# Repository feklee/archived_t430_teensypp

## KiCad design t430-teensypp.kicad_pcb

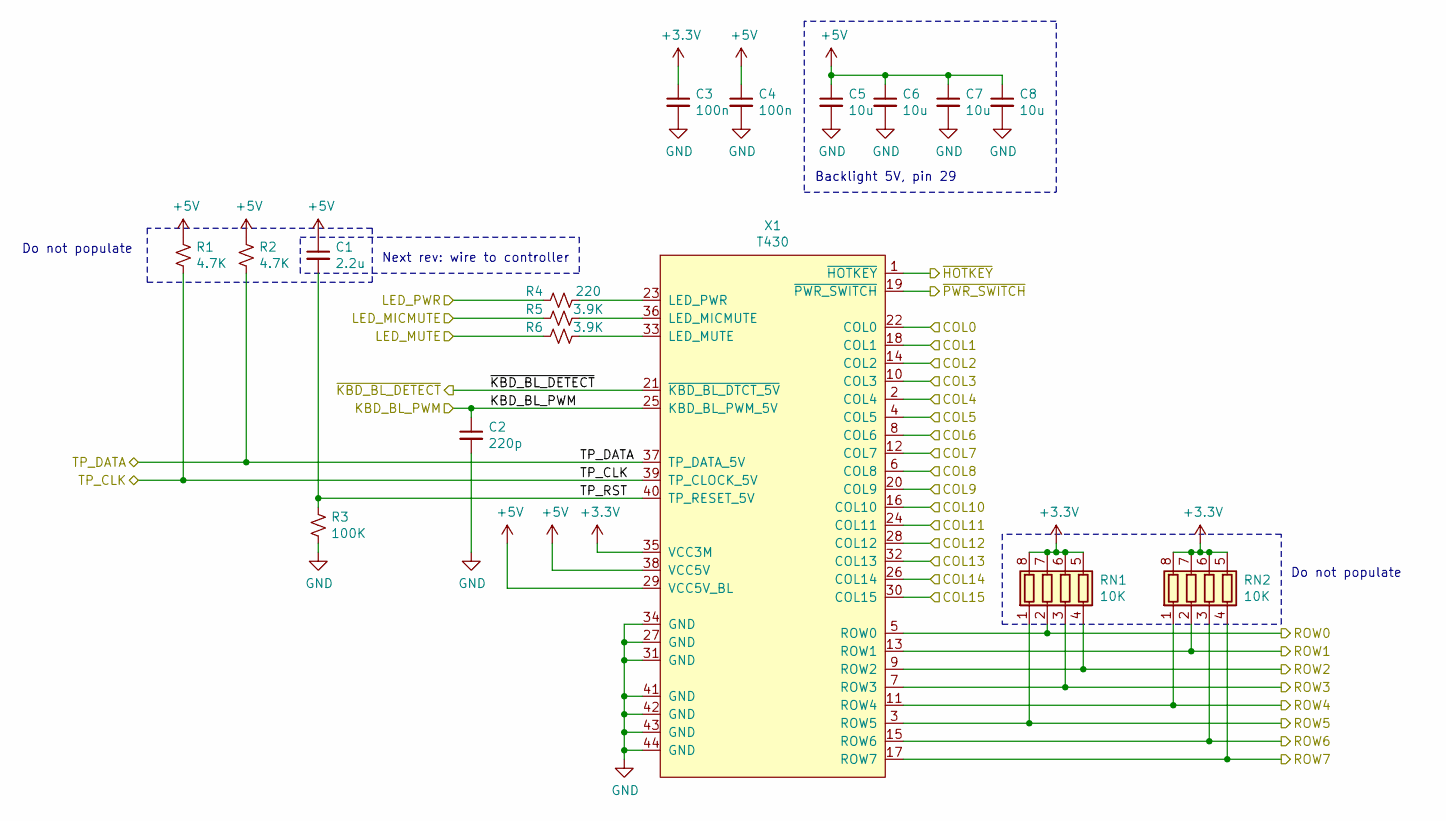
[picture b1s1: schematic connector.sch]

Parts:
C1: 2.2u; C_0805_2012Metric_Pad1.15x1.40mm_HandSolder
C2: 220p; C_0603_1608Metric
C3, C4: 100n; C_0603_1608Metric
C5, C6, C7, C8: 10u; C_0805_2012Metric_Pad1.15x1.40mm_HandSolder
R1, R2: 4.7K; R_0603_1608Metric_Pad1.05x0.95mm_HandSolder
R3: 100K; R_0603_1608Metric_Pad1.05x0.95mm_HandSolder
R4: 220; R_0603_1608Metric_Pad1.05x0.95mm_HandSolder
R5, R6: 3.9K; R_0603_1608Metric_Pad1.05x0.95mm_HandSolder
RN1, RN2: 10K; R_Array_Concave_4x0603
X1: T430

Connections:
+3V3: C3.1, RN1.5 (R4.2), RN1.6 (R3.2), RN1.7 (R2.2), RN1.8 (R1.2), RN2.5 (R4.2), RN2.6 (R3.2), RN2.7 (R2.2), RN2.8 (R1.2), X1.35 (VCC3M); also elsewhere on the board
+5V: C1.1, C4.1, C5.1, C6.1, C7.1, C8.1, R1.1, R2.1, X1.29 (VCC5V_BL), X1.38 (VCC5V); also elsewhere on the board
/Teensy2.0++/COL0: X1.22 (COL0); also elsewhere on the board
/Teensy2.0++/COL1: X1.18 (COL1); also elsewhere on the board
/Teensy2.0++/COL2: X1.14 (COL2); also elsewhere on the board
/Teensy2.0++/COL3: X1.10 (COL3); also elsewhere on the board
/Teensy2.0++/COL4: X1.2 (COL4); also elsewhere on the board
/Teensy2.0++/COL5: X1.4 (COL5); also elsewhere on the board
/Teensy2.0++/COL6: X1.8 (COL6); also elsewhere on the board
/Teensy2.0++/COL7: X1.12 (COL7); also elsewhere on the board
/Teensy2.0++/COL8: X1.6 (COL8); also elsewhere on the board
/Teensy2.0++/COL9: X1.20 (COL9); also elsewhere on the board
/Teensy2.0++/COL10: X1.16 (COL10); also elsewhere on the board
/Teensy2.0++/COL11: X1.24 (COL11); also elsewhere on the board
/Teensy2.0++/COL12: X1.28 (COL12); also elsewhere on the board
/Teensy2.0++/COL13: X1.32 (COL13); also elsewhere on the board
/Teensy2.0++/COL14: X1.26 (COL14); also elsewhere on the board
/Teensy2.0++/COL15: X1.30 (COL15); also elsewhere on the board
/Teensy2.0++/KBD_BL_PWM: C2.1, X1.25 (KBD_BL_PWM_5V); also elsewhere on the board
/Teensy2.0++/LED_MICMUTE: R5.2; also elsewhere on the board
/Teensy2.0++/LED_MUTE: R6.2; also elsewhere on the board
/Teensy2.0++/LED_PWR: R4.2; also elsewhere on the board
/Teensy2.0++/ROW0: RN1.2 (R2.1), X1.5 (ROW0); also elsewhere on the board
/Teensy2.0++/ROW1: RN2.2 (R2.1), X1.13 (ROW1); also elsewhere on the board
/Teensy2.0++/ROW2: RN1.4 (R4.1), X1.9 (ROW2); also elsewhere on the board
/Teensy2.0++/ROW3: RN1.3 (R3.1), X1.7 (ROW3); also elsewhere on the board
/Teensy2.0++/ROW4: RN2.1 (R1.1), X1.11 (ROW4); also elsewhere on the board
/Teensy2.0++/ROW5: RN1.1 (R1.1), X1.3 (ROW5); also elsewhere on the board
/Teensy2.0++/ROW6: RN2.3 (R3.1), X1.15 (ROW6); also elsewhere on the board
/Teensy2.0++/ROW7: RN2.4 (R4.1), X1.17 (ROW7); also elsewhere on the board
/Teensy2.0++/TP_CLK: R1.2, X1.39 (TP_CLOCK_5V); also elsewhere on the board
/Teensy2.0++/TP_DATA: R2.2, X1.37 (TP_DATA_5V); also elsewhere on the board
/Teensy2.0++/~HOTKEY: X1.1 (~HOTKEY); also elsewhere on the board
/Teensy2.0++/~KBD_BL_DETECT: X1.21 (~KBD_BL_DTCT_5V); also elsewhere on the board
/Teensy2.0++/~PWR_SWITCH: X1.19 (~PWR_SWITCH); also elsewhere on the board
/t430-connector/TP_RST: C1.2, R3.1, X1.40 (TP_RESET_5V)
GND: C2.2, C3.2, C4.2, C5.2, C6.2, C7.2, C8.2, R3.2, X1.27 (GND), X1.31 (GND), X1.34 (GND), X1.41 (GND), X1.42 (GND), X1.43 (GND), X1.44 (GND); also elsewhere on the board
unnamed: R4.1, X1.23 (LED_PWR)
unnamed: R5.1, X1.36 (LED_MICMUTE)
unnamed: R6.1, X1.33 (LED_MUTE)

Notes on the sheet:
Backlight 5V, pin 29
Do not populate
Next rev: wire to controller

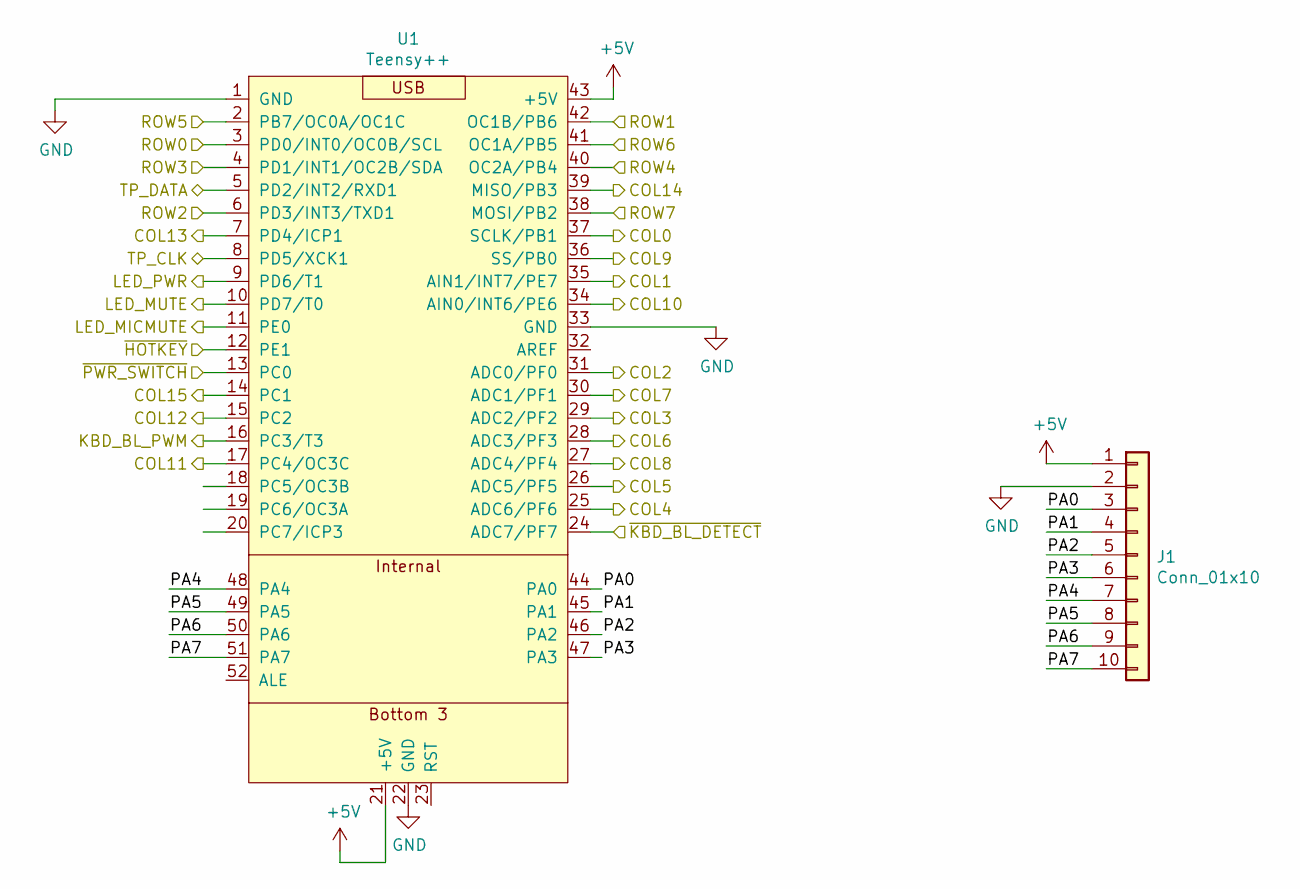
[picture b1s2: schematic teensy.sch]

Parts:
J1: Conn_01x10; PinSocket_1x10_P2.54mm_Vertical
U1: Teensy++; Teensy2.0++

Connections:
+5V: J1.1, U1.21 (+5V), U1.43 (+5V); also elsewhere on the board
/Teensy2.0++/COL0: U1.37 (SCLK/PB1); also elsewhere on the board
/Teensy2.0++/COL1: U1.35 (AIN1/INT7/PE7); also elsewhere on the board
/Teensy2.0++/COL2: U1.31 (ADC0/PF0); also elsewhere on the board
/Teensy2.0++/COL3: U1.29 (ADC2/PF2); also elsewhere on the board
/Teensy2.0++/COL4: U1.25 (ADC6/PF6); also elsewhere on the board
/Teensy2.0++/COL5: U1.26 (ADC5/PF5); also elsewhere on the board
/Teensy2.0++/COL6: U1.28 (ADC3/PF3); also elsewhere on the board
/Teensy2.0++/COL7: U1.30 (ADC1/PF1); also elsewhere on the board
/Teensy2.0++/COL8: U1.27 (ADC4/PF4); also elsewhere on the board
/Teensy2.0++/COL9: U1.36 (SS/PB0); also elsewhere on the board
/Teensy2.0++/COL10: U1.34 (AIN0/INT6/PE6); also elsewhere on the board
/Teensy2.0++/COL11: U1.17 (PC4/OC3C); also elsewhere on the board
/Teensy2.0++/COL12: U1.15 (PC2); also elsewhere on the board
/Teensy2.0++/COL13: U1.7 (PD4/ICP1); also elsewhere on the board
/Teensy2.0++/COL14: U1.39 (MISO/PB3); also elsewhere on the board
/Teensy2.0++/COL15: U1.14 (PC1); also elsewhere on the board
/Teensy2.0++/KBD_BL_PWM: U1.16 (PC3/T3); also elsewhere on the board
/Teensy2.0++/LED_MICMUTE: U1.11 (PE0); also elsewhere on the board
/Teensy2.0++/LED_MUTE: U1.10 (PD7/T0); also elsewhere on the board
/Teensy2.0++/LED_PWR: U1.9 (PD6/T1); also elsewhere on the board
/Teensy2.0++/PA0: J1.3, U1.44 (PA0)
/Teensy2.0++/PA1: J1.4, U1.45 (PA1)
/Teensy2.0++/PA2: J1.5, U1.46 (PA2)
/Teensy2.0++/PA3: J1.6, U1.47 (PA3)
/Teensy2.0++/PA4: J1.7, U1.48 (PA4)
/Teensy2.0++/PA5: J1.8, U1.49 (PA5)
/Teensy2.0++/PA6: J1.9, U1.50 (PA6)
/Teensy2.0++/PA7: J1.10, U1.51 (PA7)
/Teensy2.0++/ROW0: U1.3 (PD0/INT0/OC0B/SCL); also elsewhere on the board
/Teensy2.0++/ROW1: U1.42 (OC1B/PB6); also elsewhere on the board
/Teensy2.0++/ROW2: U1.6 (PD3/INT3/TXD1); also elsewhere on the board
/Teensy2.0++/ROW3: U1.4 (PD1/INT1/OC2B/SDA); also elsewhere on the board
/Teensy2.0++/ROW4: U1.40 (OC2A/PB4); also elsewhere on the board
/Teensy2.0++/ROW5: U1.2 (PB7/OC0A/OC1C); also elsewhere on the board
/Teensy2.0++/ROW6: U1.41 (OC1A/PB5); also elsewhere on the board
/Teensy2.0++/ROW7: U1.38 (MOSI/PB2); also elsewhere on the board
/Teensy2.0++/TP_CLK: U1.8 (PD5/XCK1); also elsewhere on the board
/Teensy2.0++/TP_DATA: U1.5 (PD2/INT2/RXD1); also elsewhere on the board
/Teensy2.0++/~HOTKEY: U1.12 (PE1); also elsewhere on the board
/Teensy2.0++/~KBD_BL_DETECT: U1.24 (ADC7/PF7); also elsewhere on the board
/Teensy2.0++/~PWR_SWITCH: U1.13 (PC0); also elsewhere on the board
GND: J1.2, U1.1 (GND), U1.22 (GND), U1.33 (GND); also elsewhere on the board

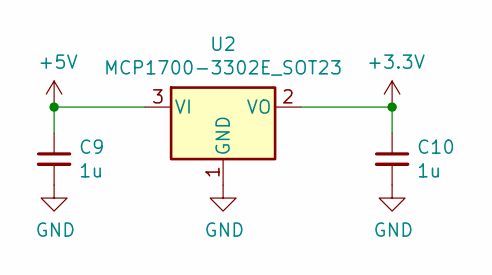
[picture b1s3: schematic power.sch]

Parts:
C9, C10: 1u; C_0805_2012Metric_Pad1.15x1.40mm_HandSolder
U2: MCP1700-3302E_SOT23; SOT-23

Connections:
+3V3: C10.1, U2.2 (VO); also elsewhere on the board
+5V: C9.1, U2.3 (VI); also elsewhere on the board
GND: C9.2, C10.2, U2.1 (GND); also elsewhere on the board

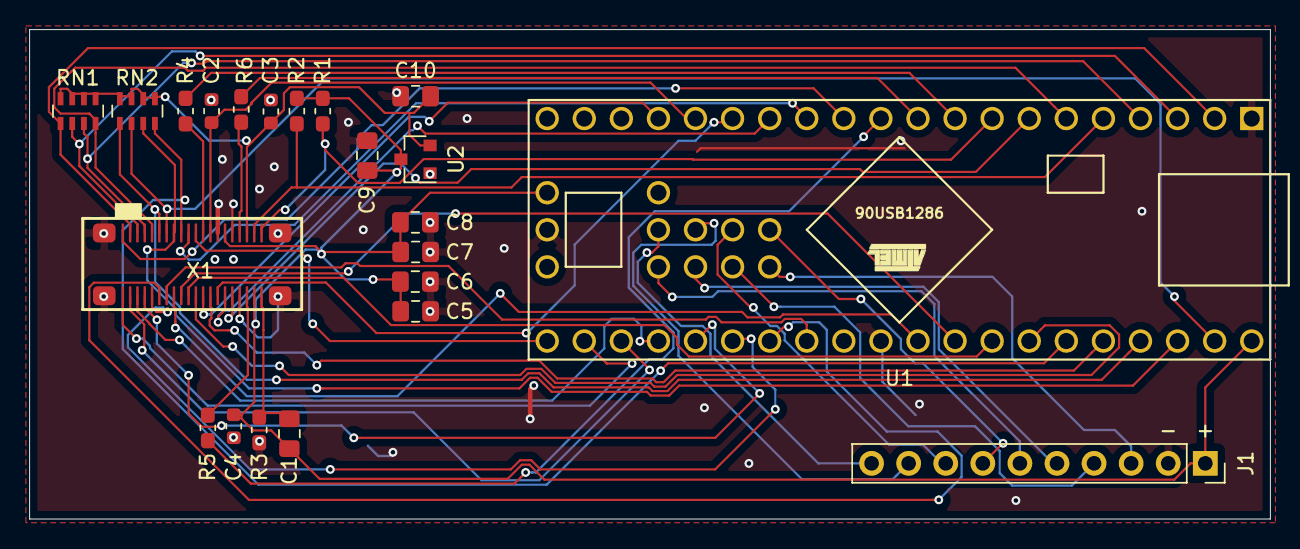
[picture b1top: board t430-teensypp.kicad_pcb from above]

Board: 2 copper layers, 85.0 x 33.5 mm, 22 parts (0 on the bottom side), 48 nets.

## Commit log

2019-07-29 nearly perfect until found out Teensy++ only have 1 USART
2019-08-05 Updated footprints and started PCB
2019-08-06 Started mapping traces
2019-08-13 Routed to 6/6
2019-11-22 T430 pinout should be aligned now
2019-11-23 Added 'do not populate' for Trackpoint and rows
2019-11-23 Added next revisions comments
2020-08-11 Add holes for Teensy
2020-08-31 Add photo of PCB
